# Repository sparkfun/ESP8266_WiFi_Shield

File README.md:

SparkFun ESP8266 WiFi Shield
========================================

[*SparkFun ESP8266 WiFi Shield (WRL-13287)*](https://www.sparkfun.com/products/13287)

The [SparkFun ESP8266 WiFi Shield](https://www.sparkfun.com/products/13287) is essentially an Arduino shield for the ESP8266 WiFi SoC. The ESP8266 ships with a slightly customized version of the Espressif AT command set.

The ESP8266 is controlled by serial AT commands. The shield is equipped with a switch to swap between a software serial port or hardware serial port interface.

Repository Contents
-------------------

* **/Firmware** - Firmware flashed on the ESP8266 WiFi Shield (requires ESP8266 SDK 1.2.0)
* **/Hardware** - Eagle design files (.brd, .sch)
* **/Production** - Production panel files (.brd)

Documentation
--------------
* **[Hookup Guide](https://learn.sparkfun.com/tutorials/esp8266-wifi-shield-hookup-guide)** - Exhaustive hookup guide for the ESP8266 WiFi Shield.

Product Versions
----------------
* [DEV-13287](https://www.sparkfun.com/products/13287)- V1.0 release of the WiFi Shield.

License Information
-------------------
This product is _**open source**_! 

The **hardware** is released under [Creative Commons ShareAlike 4.0 International](https://creativecommons.org/licenses/by-sa/4.0/).

The **code** is beerware; if you see me (or any other SparkFun employee) at the local, and you've found our code helpful, please buy us a round!

Please use, reuse, and modify these files as you see fit. Please maintain attribution to SparkFun Electronics and release anyWiFi Shield derivative under the same license.

Distributed as-is; no warranty is given.

- Your friends at SparkFun.

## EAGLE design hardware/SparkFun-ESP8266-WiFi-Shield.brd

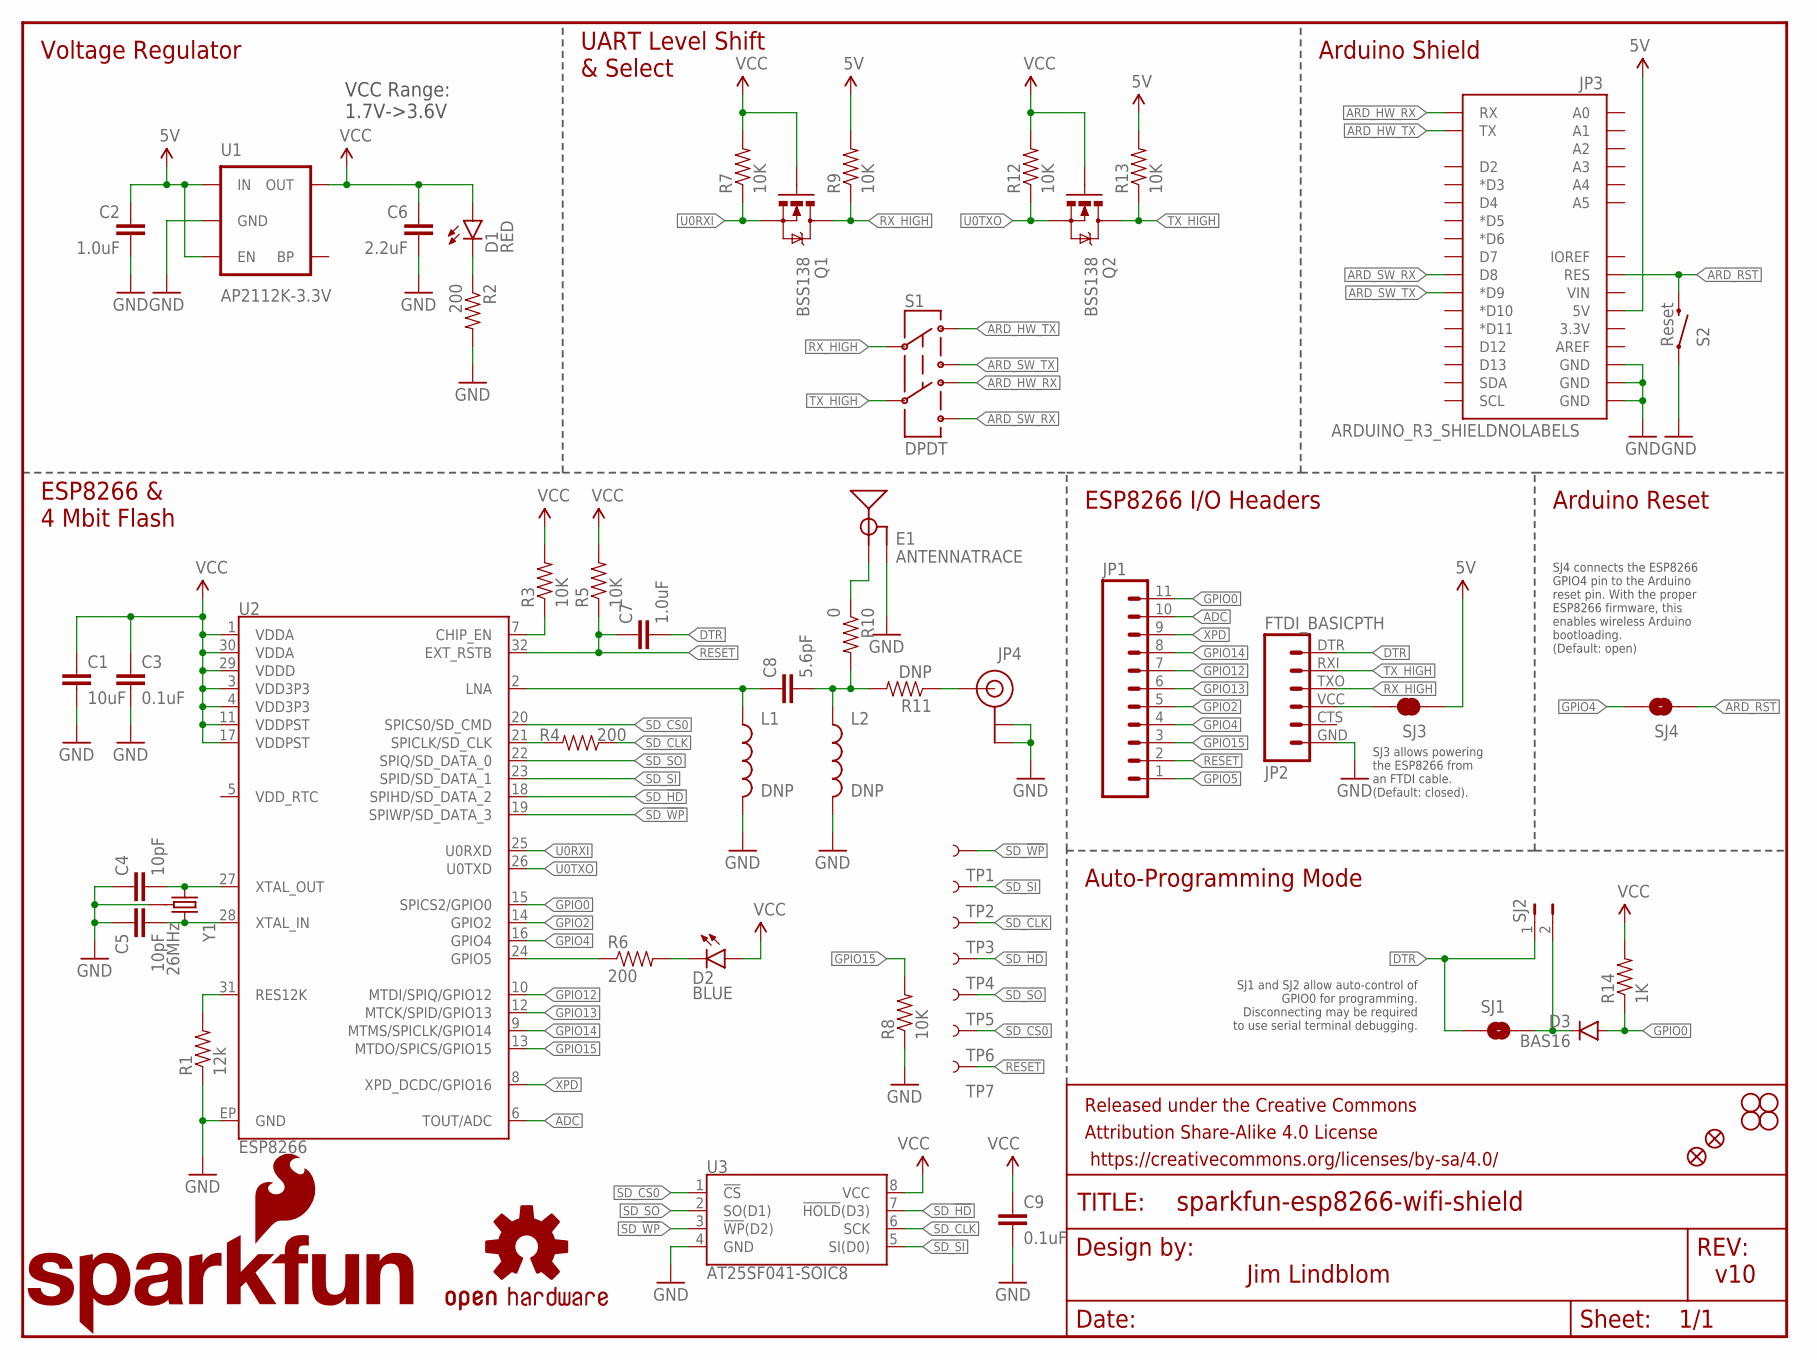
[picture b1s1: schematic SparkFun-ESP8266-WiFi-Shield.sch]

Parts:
C1: 10uF; 0603-CAP
C2: 1.0uF; 0805
C3, C9: 0.1uF; 0603-CAP
C4, C5: 10pF; 0603-CAP
C6: 2.2uF; 0603-CAP
C7: 1.0uF; 0603-CAP
C8: 5.6pF; 0603-CAP
D1: RED; LED-0603
D2: BLUE; LED-0603
D3: BAS16; SOD-323
E1: ANTENNATRACE; TRACE_ANTENNA_2.4GHZ_25.7MM
FID1, FID2: FIDUCIAL1X2; FIDUCIAL-1X2
FRAME1: FRAME-LETTER; CREATIVE_COMMONS
JP1: M11PTH; 1X11
JP2: FTDI_BASICPTH; FTDI_BASIC
JP3: ARDUINO_R3_SHIELDNOLABELS; UNO_R3_SHIELD_NOLABELS
JP4: U.FL
L1, L2: DNP; 0603
LOGO1: SFE_LOGO_NAME_FLAME.2_INCH; SFE_LOGO_NAME_FLAME_.2
LOGO2: OSHW-LOGOM; OSHW-LOGO-M
Q1, Q2: BSS138; SOT23-3
R1: 12k; 0603-RES
R2, R4, R6: 200; 0603-RES
R3, R5, R7, R8, R9, R12, R13: 10K; 0603-RES
R10: 0; 0603
R11: DNP; 0603-RES
R14: 1K; 0603-RES
S1: DPDT; AYZ0202
S2: Reset; TACTILE-SWITCH-SMD
SJ1: JUMPER-PAD-2-NO; PAD-JUMPER-2-NO_NO_SILK
SJ2: JUMPER-PTH-2-NO; PTH-JUMPER-2-NO_NO_SILK
SJ3: JUMPER-PAD-2-NC_BY_TRACE; PAD-JUMPER-2-NC_BY_TRACE_YES_SILK
SJ4: JUMPER-PAD-2-NOYES_SILK; PAD-JUMPER-2-NO_YES_SILK
STANDOFF1, STANDOFF2, STANDOFF3, STANDOFF4: STAND-OFF
TP1, TP2, TP3, TP4, TP5, TP6, TP7: TEST-POINT3X5; PAD.03X.05
U1: AP2112K-3.3V; SOT23-5
U2: ESP8266; QFN32
U3: AT25SF041-SOIC8; SO08
Y1: 26MHz; CRYSTAL-SMD-3.2X2.5

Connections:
5V: C2.1, JP3.5V, R9.2, R13.2, SJ3.1, U1.1 (IN), U1.3 (EN)
ADC: JP1.10, U2.6 (TOUT/ADC)
ANT: JP4.P$3 (SIGNAL), R11.1
ARD_HW_RX: JP3.RX, S1.4
ARD_HW_TX: JP3.TX, S1.1
ARD_RST: JP3.RES, S2.3 (2), SJ4.1
ARD_SW_RX: JP3.D8, S1.6
ARD_SW_TX: JP3.D9 (*D9), S1.3
CHIP_EN: R3.1, U2.7 (CHIP_EN)
DTR: C7.2, JP2.DTR (1), SJ1.1, SJ2.1
GND: C1.2, C2.2, C3.2, C4.1, C5.1, C6.2, C9.2, E1.GND, E1.GND2 (GND), JP2.GND (6), JP3.GND@0 (GND), JP3.GND@1 (GND), JP3.GND@2 (GND), JP4.P$1 (GND), JP4.P$2 (GND), L1.2, L2.2, R1.1, R2.2, R8.1, S2.1, U1.2 (GND), U2.EP (GND), U3.4 (GND), Y1.2 (GND), Y1.4 (GND)
GPIO0: D3.A, JP1.11, R14.1, U2.15 (SPICS2/GPIO0)
GPIO2: JP1.5, U2.14 (GPIO2)
GPIO4: JP1.4, SJ4.2, U2.16 (GPIO4)
GPIO5: JP1.1, R6.1, U2.24 (GPIO5)
GPIO12: JP1.7, U2.10 (MTDI/SPIQ/GPIO12)
GPIO13: JP1.6, U2.12 (MTCK/SPID/GPIO13)
GPIO14: JP1.8, U2.9 (MTMS/SPICLK/GPIO14)
GPIO15: JP1.3, R8.2, U2.13 (MTDO/SPICS/GPIO15)
LNA: C8.1, L1.1, U2.2 (LNA)
unnamed: R1.2, U2.31 (RES12K)
unnamed: C5.2, U2.28 (XTAL_IN), Y1.3 (2)
unnamed: C4.2, U2.27 (XTAL_OUT), Y1.1
unnamed: D1.C, R2.1
unnamed: C8.2, L2.1, R10.2, R11.2
unnamed: R4.2, U2.21 (SPICLK/SD_CLK)
unnamed: JP2.VCC (4), SJ3.2
unnamed: D2.C, R6.2
RESET: C7.1, JP1.2, R5.1, TP7.P$1, U2.32 (EXT_RSTB)
RX_HIGH: JP2.TXO (3), Q1.3 (D), R9.1, S1.2
SD_!HD!: TP4.P$1, U2.18 (SPIHD/SD_DATA_2), U3.7 (!HOLD!(D3))
SD_!WP!: TP1.P$1, U2.19 (SPIWP/SD_DATA_3), U3.3 (!WP!(D2))
SD_CLK: R4.1, TP3.P$1, U3.6 (SCK)
SD_CS0: TP6.P$1, U2.20 (SPICS0/SD_CMD), U3.1 (!CS!)
SD_SI: TP2.P$1, U2.23 (SPID/SD_DATA_1), U3.5 (SI(D0))
SD_SO: TP5.P$1, U2.22 (SPIQ/SD_DATA_0), U3.2 (SO(D1))
SJ2: D3.C, SJ1.2, SJ2.2
TRACE_ANT: E1.ANT (SIGNAL), R10.1
TX_HIGH: JP2.RXI (2), Q2.3 (D), R13.1, S1.5
U0RXI: Q1.2 (S), R7.1, U2.25 (U0RXD)
U0TXO: Q2.2 (S), R12.1, U2.26 (U0TXD)
VCC: C1.1, C3.1, C6.1, C9.1, D1.A, D2.A, Q1.1 (G), Q2.1 (G), R3.2, R5.2, R7.2, R12.2, R14.2, U1.5 (OUT), U2.1 (VDDA), U2.3 (VDD3P3), U2.4 (VDD3P3), U2.11 (VDDPST), U2.17 (VDDPST), U2.29 (VDDD), U2.30 (VDDA), U3.8 (VCC)
XPD: JP1.9, U2.8 (XPD_DCDC/GPIO16)

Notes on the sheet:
VCC Range: 1.7V->3.6V
SJ1 and SJ2 allow auto-control of GPIO0 for programming. Disconnecting may be required to use serial terminal debugging.
Auto-Programming Mode
ESP8266 I/O Headers
Arduino Shield
UART Level Shift & Select
Voltage Regulator
ESP8266 & 4 Mbit Flash
v10
Jim Lindblom
Arduino Reset
SJ4 connects the ESP8266 GPIO4 pin to the Arduino reset pin. With the proper ESP8266 firmware, this enables wireless Arduino bootloading. (Default: open)
SJ3 allows powering the ESP8266 from an FTDI cable. (Default: closed).

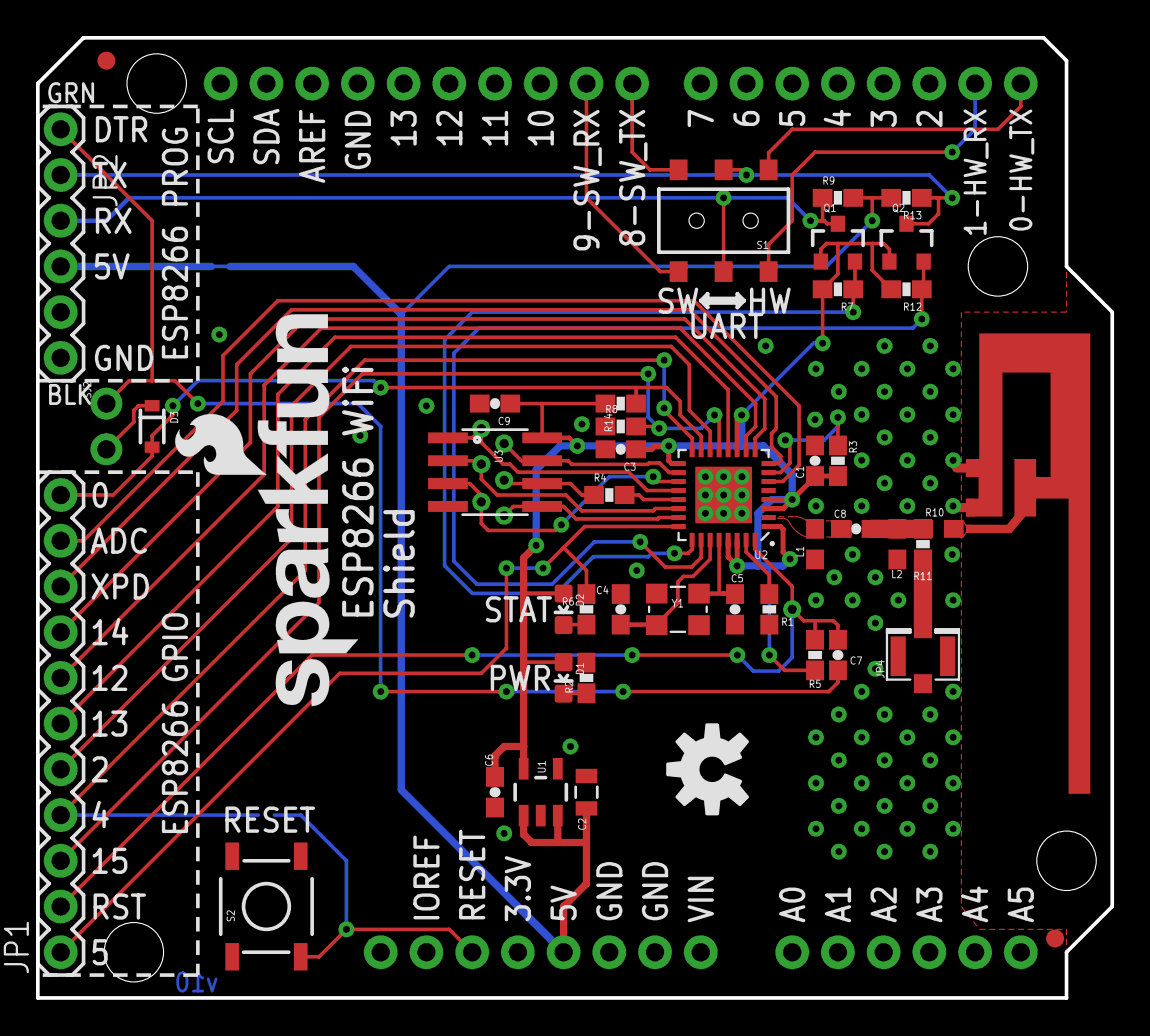
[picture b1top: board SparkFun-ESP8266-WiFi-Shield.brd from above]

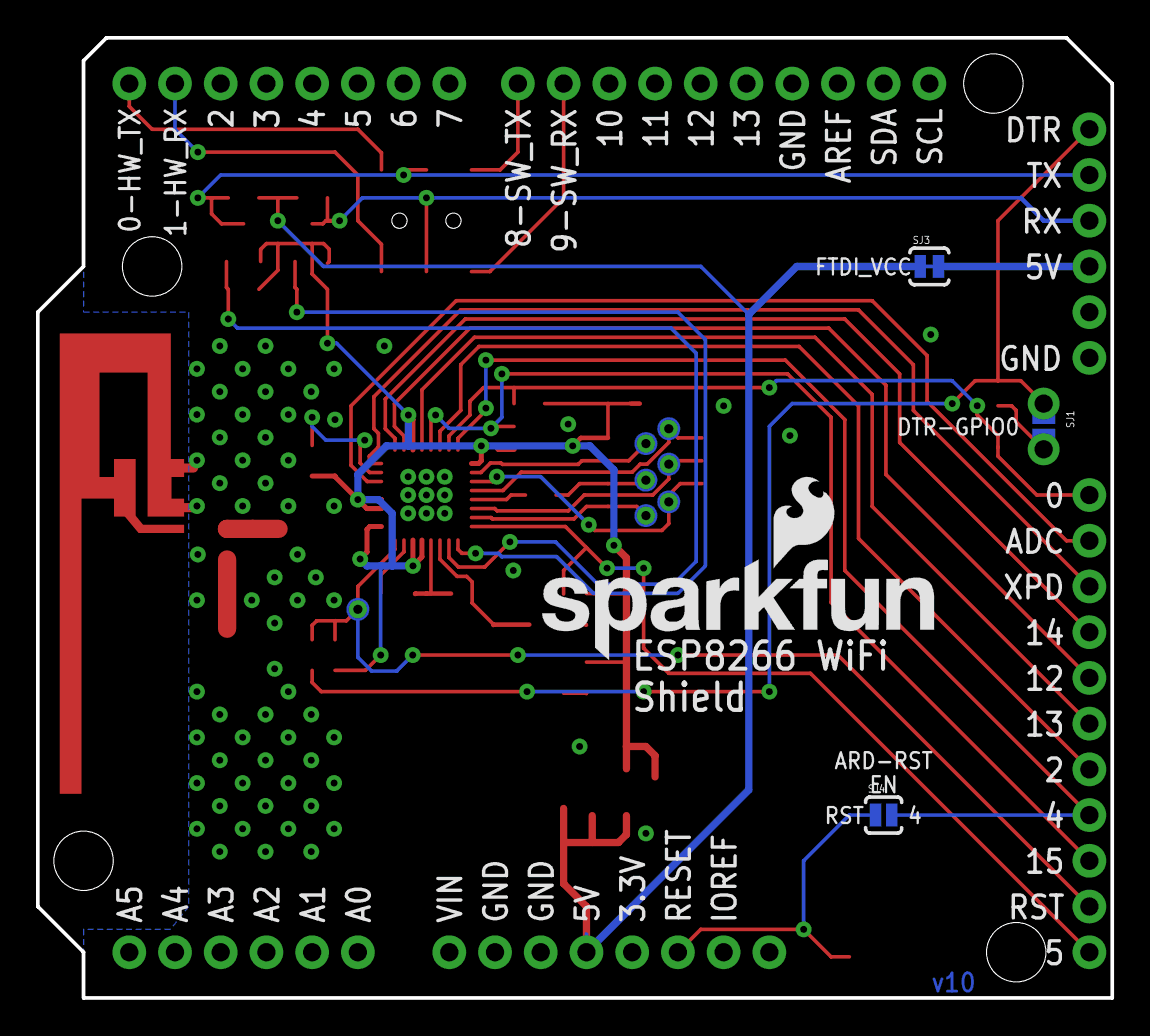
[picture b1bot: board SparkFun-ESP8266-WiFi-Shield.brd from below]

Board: 2 copper layers, 59.7 x 53.3 mm, 62 parts (11 on the bottom side), 43 nets.

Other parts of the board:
LOGO3: SFE_LOGO_NAME_FLAME.2_INCH; SFE_LOGO_NAME_FLAME_.2

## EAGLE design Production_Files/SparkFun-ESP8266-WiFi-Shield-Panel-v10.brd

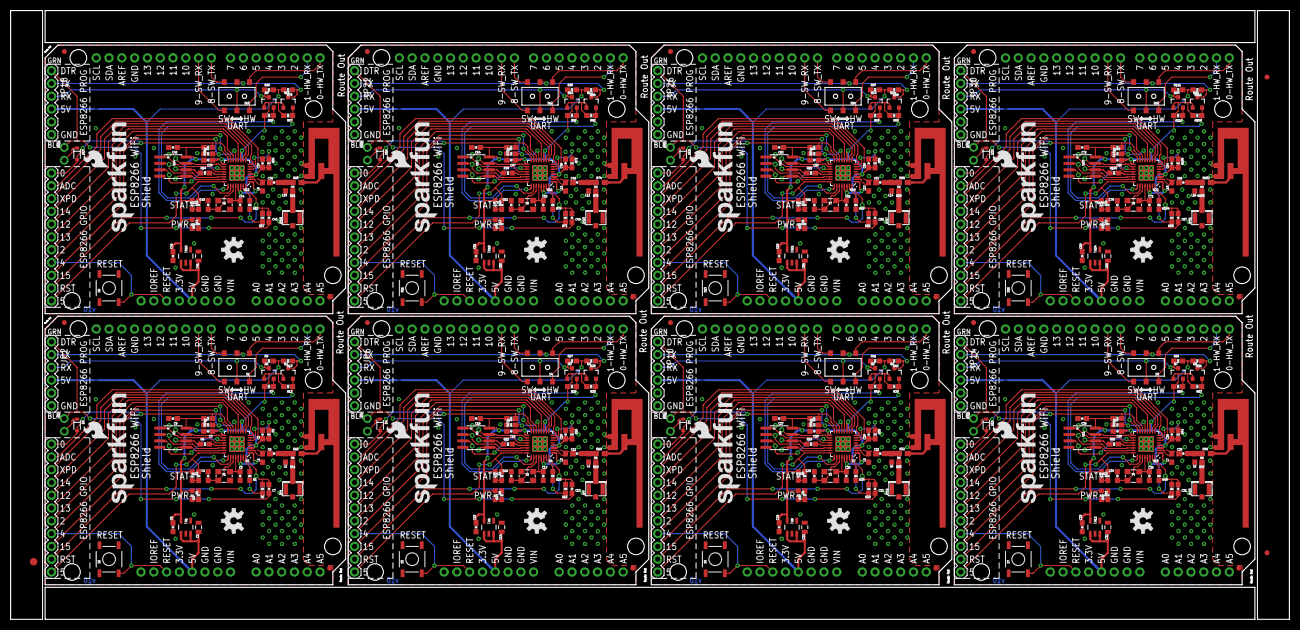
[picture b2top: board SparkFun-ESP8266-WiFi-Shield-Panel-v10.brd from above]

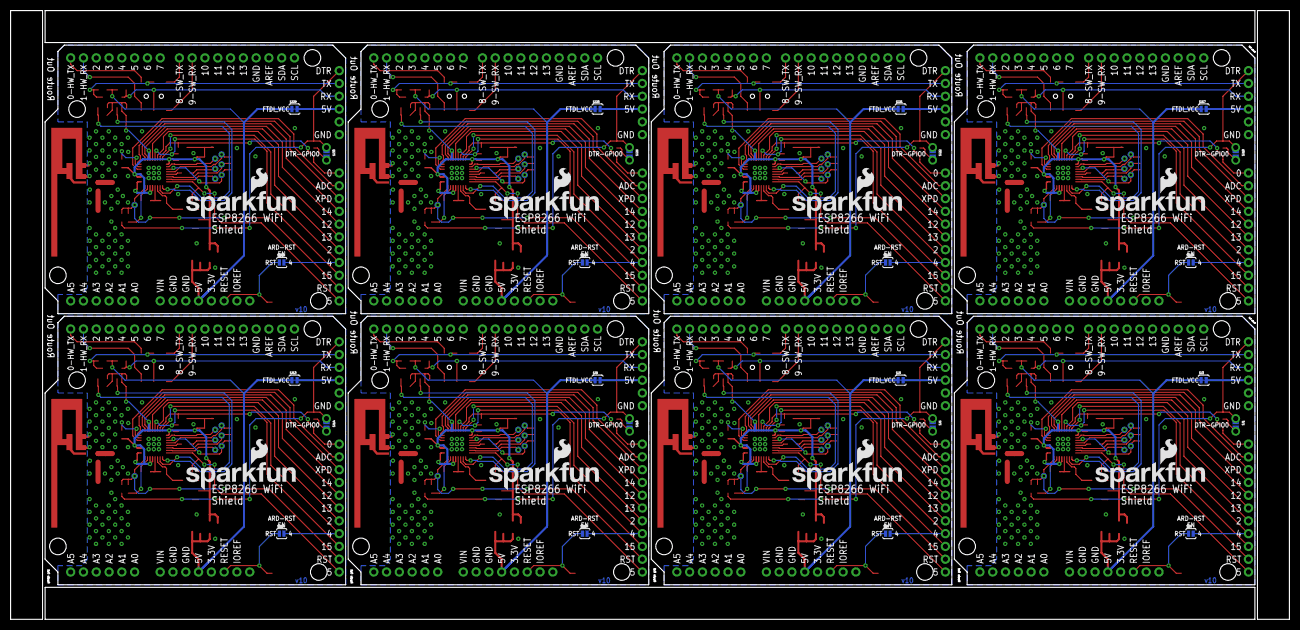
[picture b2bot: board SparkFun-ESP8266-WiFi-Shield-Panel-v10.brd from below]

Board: 2 copper layers, 254.0 x 120.9 mm, 491 parts (88 on the bottom side), 344 nets.

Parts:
C1, C10, C19, C28, C37, C46, C55, C64: 10uF; 0603-CAP
C2, C14, C23, C32, C41, C50, C59, C68: 1.0uF; 0805
C3, C9, C11, C18, C20, C27, C29, C36, C38, C45, C47, C54, C56, C63, C65, C72: 0.1uF; 0603-CAP
C4, C5, C16, C17, C25, C26, C34, C35, C43, C44, C52, C53, C61, C62, C70, C71: 10pF; 0603-CAP
C6, C15, C24, C33, C42, C51, C60, C69: 2.2uF; 0603-CAP
C7, C13, C22, C31, C40, C49, C58, C67: 1.0uF; 0603-CAP
C8, C12, C21, C30, C39, C48, C57, C66: 5.6pF; 0603-CAP
D1, D5, D8, D11, D14, D17, D20, D23: RED; LED-0603
D2, D6, D9, D12, D15, D18, D21, D24: BLUE; LED-0603
D3, D4, D7, D10, D13, D16, D19, D22: BAS16; SOD-323
E1, E2, E3, E4, E5, E6, E7, E8: ANTENNATRACE; TRACE_ANTENNA_2.4GHZ_25.7MM
E$1: FIDUCIAL-1.5X3
E$4, E$5: FIDUCIAL-1X2
FID1, FID2, FID3, FID4, FID5, FID6, FID7, FID8, FID9, FID10, FID11, FID12, FID13, FID14, FID15, FID16: FIDUCIAL1X2; FIDUCIAL-1X2
JP1, JP8, JP12, JP16, JP20, JP24, JP28, JP32: 1X11
JP2, JP6, JP10, JP14, JP18, JP22, JP26, JP30: FTDI_BASICPTH; FTDI_BASIC
JP3, JP5, JP9, JP13, JP17, JP21, JP25, JP29: ARDUINO_R3_SHIELDNOLABELS; UNO_R3_SHIELD_NOLABELS
JP4, JP7, JP11, JP15, JP19, JP23, JP27, JP31: U.FL
L1, L2, L3, L4, L5, L6, L7, L8, L9, L10, L11, L12, L13, L14, L15, L16: DNP; 0603
LOGO1, LOGO3, LOGO5, LOGO6, LOGO8, LOGO9, LOGO11, LOGO12, LOGO14, LOGO15, LOGO17, LOGO18, LOGO20, LOGO21, LOGO23, LOGO24: SFE_LOGO_NAME_FLAME.2_INCH; SFE_LOGO_NAME_FLAME_.2
LOGO2, LOGO4, LOGO7, LOGO10, LOGO13, LOGO16, LOGO19, LOGO22: OSHW-LOGOM; OSHW-LOGO-M
Q1, Q2, Q3, Q4, Q5, Q6, Q7, Q8, Q9, Q10, Q11, Q12, Q13, Q14, Q15, Q16: BSS138; SOT23-3
R1, R20, R34, R48, R62, R76, R90, R104: 12k; 0603-RES
R2, R4, R6, R21, R22, R23, R35, R36, R37, R49, R50, R51, R63, R64, R65, R77, R78, R79, R91, R92, R93, R105, R106, R107: 200; 0603-RES
R3, R5, R7, R8, R9, R12, R13, R15, R16, R24, R25, R26, R27, R28, R29, R30, R38, R39, R40, R41, R42, R43, R44, R52, R53, R54, R55, R56, R57, R58, R66, R67, R68, R69, R70, R71, R72, R80, R81, R82, R83, R84, R85, R86, R94, R95, R96, R97, R98, R99, R100, R108, R109, R110, R111, R112: 10K; 0603-RES
R10, R18, R32, R46, R60, R74, R88, R102: 0; 0603
R11, R19, R33, R47, R61, R75, R89, R103: DNP; 0603-RES
R14, R17, R31, R45, R59, R73, R87, R101: 1K; 0603-RES
S1, S4, S6, S8, S10, S12, S14, S16: DPDT; AYZ0202
S2, S3, S5, S7, S9, S11, S13, S15: Reset; TACTILE-SWITCH-SMD
SJ1, SJ6, SJ10, SJ14, SJ18, SJ22, SJ26, SJ30: PAD-JUMPER-2-NO_NO_SILK
SJ2, SJ7, SJ11, SJ15, SJ19, SJ23, SJ27, SJ31: PTH-JUMPER-2-NO_NO_SILK
SJ3, SJ5, SJ9, SJ13, SJ17, SJ21, SJ25, SJ29: PAD-JUMPER-2-NC_BY_TRACE_YES_SILK
SJ4, SJ8, SJ12, SJ16, SJ20, SJ24, SJ28, SJ32: PAD-JUMPER-2-NO_YES_SILK
STANDOFF1, STANDOFF2, STANDOFF3, STANDOFF4, STANDOFF5, STANDOFF6, STANDOFF7, STANDOFF8, STANDOFF9, STANDOFF10, STANDOFF11, STANDOFF12, STANDOFF13, STANDOFF14, STANDOFF15, STANDOFF16, STANDOFF17, STANDOFF18, STANDOFF19, STANDOFF20, STANDOFF21, STANDOFF22, STANDOFF23, STANDOFF24, STANDOFF25, STANDOFF26, STANDOFF27, STANDOFF28, STANDOFF29, STANDOFF30, STANDOFF31, STANDOFF32: STAND-OFF
TP1, TP2, TP3, TP4, TP5, TP6, TP7, TP8, TP9, TP10, TP11, TP12, TP13, TP14, TP15, TP16, TP17, TP18, TP19, TP20, TP21, TP22, TP23, TP24, TP25, TP26, TP27, TP28, TP29, TP30, TP31, TP32, TP33, TP34, TP35, TP36, TP37, TP38, TP39, TP40, TP41, TP42, TP43, TP44, TP45, TP46, TP47, TP48, TP49, TP50, TP51, TP52, TP53, TP54, TP55, TP56: PAD.03X.05
U1, U6, U9, U12, U15, U18, U21, U24: AP2112K-3.3V; SOT23-5
U2, U4, U7, U10, U13, U16, U19, U22: ESP8266; QFN32
U3, U5, U8, U11, U14, U17, U20, U23: AT25SF041-SOIC8; SO08
Y1, Y2, Y3, Y4, Y5, Y6, Y7, Y8: 26MHz; CRYSTAL-SMD-3.2X2.5

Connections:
5V: C2.1, JP3.5V, R9.2, R13.2, SJ3.1, U1.1, U1.3
5V1: C14.1, JP5.5V, R27.2, R28.2, SJ5.1, U6.1, U6.3
5V2: C23.1, JP9.5V, R41.2, R42.2, SJ9.1, U9.1, U9.3
5V3: C32.1, JP13.5V, R55.2, R56.2, SJ13.1, U12.1, U12.3
5V4: C41.1, JP17.5V, R69.2, R70.2, SJ17.1, U15.1, U15.3
5V5: C50.1, JP21.5V, R83.2, R84.2, SJ21.1, U18.1, U18.3
5V6: C59.1, JP25.5V, R97.2, R98.2, SJ25.1, U21.1, U21.3
5V7: C68.1, JP29.5V, R111.2, R112.2, SJ29.1, U24.1, U24.3
ADC: JP1.10, U2.6
ADC1: JP8.10, U4.6
ADC2: JP12.10, U7.6
ADC3: JP16.10, U10.6
ADC4: JP20.10, U13.6
ADC5: JP24.10, U16.6
ADC6: JP28.10, U19.6
ADC7: JP32.10, U22.6
ANT: JP4.P$3, R11.1
ANT1: JP7.P$3, R19.1
ANT2: JP11.P$3, R33.1
ANT3: JP15.P$3, R47.1
ANT4: JP19.P$3, R61.1
ANT5: JP23.P$3, R75.1
ANT6: JP27.P$3, R89.1
ANT7: JP31.P$3, R103.1
ARD_HW_RX: JP3.RX, S1.4
ARD_HW_RX1: JP5.RX, S4.4
ARD_HW_RX2: JP9.RX, S6.4
ARD_HW_RX3: JP13.RX, S8.4
ARD_HW_RX4: JP17.RX, S10.4
ARD_HW_RX5: JP21.RX, S12.4
ARD_HW_RX6: JP25.RX, S14.4
ARD_HW_RX7: JP29.RX, S16.4
ARD_HW_TX: JP3.TX, S1.1
ARD_HW_TX1: JP5.TX, S4.1
ARD_HW_TX2: JP9.TX, S6.1
ARD_HW_TX3: JP13.TX, S8.1
ARD_HW_TX4: JP17.TX, S10.1
ARD_HW_TX5: JP21.TX, S12.1
ARD_HW_TX6: JP25.TX, S14.1
ARD_HW_TX7: JP29.TX, S16.1
ARD_RST: JP3.RES, S2.3, SJ4.1
ARD_RST1: JP5.RES, S3.3, SJ8.1
ARD_RST2: JP9.RES, S5.3, SJ12.1
ARD_RST3: JP13.RES, S7.3, SJ16.1
ARD_RST4: JP17.RES, S9.3, SJ20.1
ARD_RST5: JP21.RES, S11.3, SJ24.1
ARD_RST6: JP25.RES, S13.3, SJ28.1
ARD_RST7: JP29.RES, S15.3, SJ32.1
ARD_SW_RX: JP3.D8, S1.6
ARD_SW_RX1: JP5.D8, S4.6
ARD_SW_RX2: JP9.D8, S6.6
ARD_SW_RX3: JP13.D8, S8.6
ARD_SW_RX4: JP17.D8, S10.6
ARD_SW_RX5: JP21.D8, S12.6
ARD_SW_RX6: JP25.D8, S14.6
ARD_SW_RX7: JP29.D8, S16.6
ARD_SW_TX: JP3.D9, S1.3
ARD_SW_TX1: JP5.D9, S4.3
ARD_SW_TX2: JP9.D9, S6.3
ARD_SW_TX3: JP13.D9, S8.3
ARD_SW_TX4: JP17.D9, S10.3
ARD_SW_TX5: JP21.D9, S12.3
ARD_SW_TX6: JP25.D9, S14.3
ARD_SW_TX7: JP29.D9, S16.3
CHIP_EN: R3.1, U2.7
CHIP_EN1: R16.1, U4.7
CHIP_EN2: R30.1, U7.7
CHIP_EN3: R44.1, U10.7
CHIP_EN4: R58.1, U13.7
CHIP_EN5: R72.1, U16.7
CHIP_EN6: R86.1, U19.7
CHIP_EN7: R100.1, U22.7
DTR: C7.2, JP2.DTR, SJ1.1, SJ2.1
DTR1: C13.2, JP6.DTR, SJ6.1, SJ7.1
DTR2: C22.2, JP10.DTR, SJ10.1, SJ11.1
DTR3: C31.2, JP14.DTR, SJ14.1, SJ15.1
DTR4: C40.2, JP18.DTR, SJ18.1, SJ19.1
DTR5: C49.2, JP22.DTR, SJ22.1, SJ23.1
DTR6: C58.2, JP26.DTR, SJ26.1, SJ27.1
DTR7: C67.2, JP30.DTR, SJ30.1, SJ31.1
GND: C1.2, C2.2, C3.2, C4.1, C5.1, C6.2, C9.2, E1.GND, E1.GND2, JP2.GND, JP3.GND@0, JP3.GND@1, JP3.GND@2, JP4.P$1, JP4.P$2, L1.2, L2.2, R1.1, R2.2, R8.1, S2.1, U1.2, U2.EP, U3.4, Y1.2, Y1.4
GND1: C10.2, C11.2, C14.2, C15.2, C16.1, C17.1, C18.2, E2.GND, E2.GND2, JP5.GND@0, JP5.GND@1, JP5.GND@2, JP6.GND, JP7.P$1, JP7.P$2, L3.2, L4.2, R20.1, R23.2, R24.1, S3.1, U4.EP, U5.4, U6.2, Y2.2, Y2.4
GND2: C19.2, C20.2, C23.2, C24.2, C25.1, C26.1, C27.2, E3.GND, E3.GND2, JP9.GND@0, JP9.GND@1, JP9.GND@2, JP10.GND, JP11.P$1, JP11.P$2, L5.2, L6.2, R34.1, R37.2, R38.1, S5.1, U7.EP, U8.4, U9.2, Y3.2, Y3.4
GND3: C28.2, C29.2, C32.2, C33.2, C34.1, C35.1, C36.2, E4.GND, E4.GND2, JP13.GND@0, JP13.GND@1, JP13.GND@2, JP14.GND, JP15.P$1, JP15.P$2, L7.2, L8.2, R48.1, R51.2, R52.1, S7.1, U10.EP, U11.4, U12.2, Y4.2, Y4.4
GND4: C37.2, C38.2, C41.2, C42.2, C43.1, C44.1, C45.2, E5.GND, E5.GND2, JP17.GND@0, JP17.GND@1, JP17.GND@2, JP18.GND, JP19.P$1, JP19.P$2, L9.2, L10.2, R62.1, R65.2, R66.1, S9.1, U13.EP, U14.4, U15.2, Y5.2, Y5.4
GND5: C46.2, C47.2, C50.2, C51.2, C52.1, C53.1, C54.2, E6.GND, E6.GND2, JP21.GND@0, JP21.GND@1, JP21.GND@2, JP22.GND, JP23.P$1, JP23.P$2, L11.2, L12.2, R76.1, R79.2, R80.1, S11.1, U16.EP, U17.4, U18.2, Y6.2, Y6.4
GND6: C55.2, C56.2, C59.2, C60.2, C61.1, C62.1, C63.2, E7.GND, E7.GND2, JP25.GND@0, JP25.GND@1, JP25.GND@2, JP26.GND, JP27.P$1, JP27.P$2, L13.2, L14.2, R90.1, R93.2, R94.1, S13.1, U19.EP, U20.4, U21.2, Y7.2, Y7.4
GND7: C64.2, C65.2, C68.2, C69.2, C70.1, C71.1, C72.2, E8.GND, E8.GND2, JP29.GND@0, JP29.GND@1, JP29.GND@2, JP30.GND, JP31.P$1, JP31.P$2, L15.2, L16.2, R104.1, R107.2, R108.1, S15.1, U22.EP, U23.4, U24.2, Y8.2, Y8.4
GPIO0: D3.A, JP1.11, R14.1, U2.15
GPIO1: JP8.8, U4.9
GPIO2: JP1.5, U2.14
GPIO3: D4.A, JP8.11, R17.1, U4.15
GPIO4: JP1.4, SJ4.2, U2.16
GPIO5: JP1.1, R6.1, U2.24
GPIO6: JP8.1, R21.1, U4.24
GPIO7: JP8.4, SJ8.2, U4.16
GPIO8: JP8.3, R24.2, U4.13
GPIO9: JP8.6, U4.12
GPIO10: JP8.7, U4.10
GPIO11: JP8.5, U4.14
GPIO12: JP1.7, U2.10
GPIO13: JP1.6, U2.12
GPIO14: JP1.8, U2.9
GPIO15: JP1.3, R8.2, U2.13
GPIO16: JP12.8, U7.9
GPIO17: D7.A, JP12.11, R31.1, U7.15
GPIO18: JP12.1, R35.1, U7.24
GPIO19: JP12.4, SJ12.2, U7.16
GPIO20: JP12.3, R38.2, U7.13
GPIO21: JP12.6, U7.12
GPIO22: JP12.7, U7.10
GPIO23: JP12.5, U7.14
GPIO24: JP16.8, U10.9
GPIO25: D10.A, JP16.11, R45.1, U10.15
GPIO26: JP16.1, R49.1, U10.24
GPIO27: JP16.4, SJ16.2, U10.16
GPIO28: JP16.3, R52.2, U10.13
GPIO29: JP16.6, U10.12
GPIO30: JP16.7, U10.10
GPIO31: JP16.5, U10.14
GPIO32: JP20.8, U13.9
GPIO33: D13.A, JP20.11, R59.1, U13.15
GPIO34: JP20.1, R63.1, U13.24
GPIO35: JP20.4, SJ20.2, U13.16
GPIO36: JP20.3, R66.2, U13.13
GPIO37: JP20.6, U13.12
GPIO38: JP20.7, U13.10
GPIO39: JP20.5, U13.14
GPIO40: JP24.8, U16.9
GPIO41: D16.A, JP24.11, R73.1, U16.15
GPIO42: JP24.1, R77.1, U16.24
GPIO43: JP24.4, SJ24.2, U16.16
GPIO44: JP24.3, R80.2, U16.13
GPIO45: JP24.6, U16.12
GPIO46: JP24.7, U16.10
GPIO47: JP24.5, U16.14
GPIO48: JP28.8, U19.9
GPIO49: D19.A, JP28.11, R87.1, U19.15
GPIO50: JP28.1, R91.1, U19.24
GPIO51: JP28.4, SJ28.2, U19.16
GPIO52: JP28.3, R94.2, U19.13
GPIO53: JP28.6, U19.12
GPIO54: JP28.7, U19.10
GPIO55: JP28.5, U19.14
GPIO56: JP32.8, U22.9
GPIO57: D22.A, JP32.11, R101.1, U22.15
GPIO58: JP32.1, R105.1, U22.24
GPIO59: JP32.4, SJ32.2, U22.16
GPIO60: JP32.3, R108.2, U22.13
GPIO61: JP32.6, U22.12
GPIO62: JP32.7, U22.10
GPIO63: JP32.5, U22.14
LNA: C8.1, L1.1, U2.2
LNA1: C12.1, L3.1, U4.2
LNA2: C21.1, L5.1, U7.2
LNA3: C30.1, L7.1, U10.2
LNA4: C39.1, L9.1, U13.2
LNA5: C48.1, L11.1, U16.2
LNA6: C57.1, L13.1, U19.2
LNA7: C66.1, L15.1, U22.2
unnamed: R1.2, U2.31
unnamed: C5.2, U2.28, Y1.3
unnamed: C4.2, U2.27, Y1.1
unnamed: D1.C, R2.1
unnamed: C8.2, L2.1, R10.2, R11.2
unnamed: R4.2, U2.21
unnamed: JP2.VCC, SJ3.2
unnamed: R20.2, U4.31
unnamed: D2.C, R6.2
unnamed: C17.2, U4.28, Y2.3
unnamed: C16.2, U4.27, Y2.1
unnamed: C12.2, L4.1, R18.2, R19.2
unnamed: R22.2, U4.21
unnamed: D5.C, R23.1
unnamed: JP6.VCC, SJ5.2
unnamed: D6.C, R21.2
unnamed: R34.2, U7.31
unnamed: C26.2, U7.28, Y3.3
unnamed: C25.2, U7.27, Y3.1
unnamed: C21.2, L6.1, R32.2, R33.2
unnamed: R36.2, U7.21
unnamed: D8.C, R37.1
unnamed: JP10.VCC, SJ9.2
unnamed: D9.C, R35.2
unnamed: R48.2, U10.31
unnamed: C35.2, U10.28, Y4.3
unnamed: C34.2, U10.27, Y4.1
unnamed: C30.2, L8.1, R46.2, R47.2
unnamed: R50.2, U10.21
unnamed: D11.C, R51.1
unnamed: JP14.VCC, SJ13.2
unnamed: D12.C, R49.2
unnamed: R62.2, U13.31
unnamed: C44.2, U13.28, Y5.3
unnamed: C43.2, U13.27, Y5.1
unnamed: C39.2, L10.1, R60.2, R61.2
unnamed: R64.2, U13.21
unnamed: D14.C, R65.1
unnamed: JP18.VCC, SJ17.2
unnamed: D15.C, R63.2
unnamed: R76.2, U16.31
unnamed: C53.2, U16.28, Y6.3
unnamed: C52.2, U16.27, Y6.1
unnamed: C48.2, L12.1, R74.2, R75.2
unnamed: R78.2, U16.21
unnamed: D17.C, R79.1
unnamed: JP22.VCC, SJ21.2
unnamed: D18.C, R77.2
unnamed: R90.2, U19.31
unnamed: C62.2, U19.28, Y7.3
unnamed: C61.2, U19.27, Y7.1
unnamed: C57.2, L14.1, R88.2, R89.2
unnamed: R92.2, U19.21
unnamed: D20.C, R93.1
unnamed: JP26.VCC, SJ25.2
unnamed: D21.C, R91.2
unnamed: R104.2, U22.31
unnamed: C71.2, U22.28, Y8.3
unnamed: C70.2, U22.27, Y8.1
unnamed: C66.2, L16.1, R102.2, R103.2
unnamed: R106.2, U22.21
unnamed: D23.C, R107.1
unnamed: JP30.VCC, SJ29.2
unnamed: D24.C, R105.2
RESET: C7.1, JP1.2, R5.1, TP7.P$1, U2.32
RESET1: C13.1, JP8.2, R15.1, TP8.P$1, U4.32
RESET2: C22.1, JP12.2, R29.1, TP15.P$1, U7.32
RESET3: C31.1, JP16.2, R43.1, TP22.P$1, U10.32
RESET4: C40.1, JP20.2, R57.1, TP29.P$1, U13.32
RESET5: C49.1, JP24.2, R71.1, TP36.P$1, U16.32
RESET6: C58.1, JP28.2, R85.1, TP43.P$1, U19.32
RESET7: C67.1, JP32.2, R99.1, TP50.P$1, U22.32
RX_HIGH: JP2.TXO, Q1.3, R9.1, S1.2
RX_HIGH1: JP6.TXO, Q3.3, R27.1, S4.2
RX_HIGH2: JP10.TXO, Q5.3, R41.1, S6.2
RX_HIGH3: JP14.TXO, Q7.3, R55.1, S8.2
RX_HIGH4: JP18.TXO, Q9.3, R69.1, S10.2
RX_HIGH5: JP22.TXO, Q11.3, R83.1, S12.2
RX_HIGH6: JP26.TXO, Q13.3, R97.1, S14.2
RX_HIGH7: JP30.TXO, Q15.3, R111.1, S16.2
SD_!HD!: TP4.P$1, U2.18, U3.7
SD_!HD!1: TP14.P$1, U4.18, U5.7
SD_!HD!2: TP21.P$1, U7.18, U8.7
SD_!HD!3: TP28.P$1, U10.18, U11.7
SD_!HD!4: TP35.P$1, U13.18, U14.7
SD_!HD!5: TP42.P$1, U16.18, U17.7
SD_!HD!6: TP49.P$1, U19.18, U20.7
SD_!HD!7: TP56.P$1, U22.18, U23.7
SD_!WP!: TP1.P$1, U2.19, U3.3
SD_!WP!1: TP11.P$1, U4.19, U5.3
SD_!WP!2: TP18.P$1, U7.19, U8.3
SD_!WP!3: TP25.P$1, U10.19, U11.3
SD_!WP!4: TP32.P$1, U13.19, U14.3
SD_!WP!5: TP39.P$1, U16.19, U17.3
SD_!WP!6: TP46.P$1, U19.19, U20.3
SD_!WP!7: TP53.P$1, U22.19, U23.3
SD_CLK: R4.1, TP3.P$1, U3.6
SD_CLK1: R22.1, TP13.P$1, U5.6
SD_CLK2: R36.1, TP20.P$1, U8.6
SD_CLK3: R50.1, TP27.P$1, U11.6
SD_CLK4: R64.1, TP34.P$1, U14.6
SD_CLK5: R78.1, TP41.P$1, U17.6
SD_CLK6: R92.1, TP48.P$1, U20.6
SD_CLK7: R106.1, TP55.P$1, U23.6
SD_CS0: TP6.P$1, U2.20, U3.1
SD_CS1: TP9.P$1, U4.20, U5.1
SD_CS2: TP16.P$1, U7.20, U8.1
SD_CS3: TP23.P$1, U10.20, U11.1
SD_CS4: TP30.P$1, U13.20, U14.1
SD_CS5: TP37.P$1, U16.20, U17.1
SD_CS6: TP44.P$1, U19.20, U20.1
SD_CS7: TP51.P$1, U22.20, U23.1
SD_SI: TP2.P$1, U2.23, U3.5
SD_SI1: TP12.P$1, U4.23, U5.5
SD_SI2: TP19.P$1, U7.23, U8.5
SD_SI3: TP26.P$1, U10.23, U11.5
SD_SI4: TP33.P$1, U13.23, U14.5
SD_SI5: TP40.P$1, U16.23, U17.5
SD_SI6: TP47.P$1, U19.23, U20.5
SD_SI7: TP54.P$1, U22.23, U23.5
SD_SO: TP5.P$1, U2.22, U3.2
SD_SO1: TP10.P$1, U4.22, U5.2
SD_SO2: TP17.P$1, U7.22, U8.2
SD_SO3: TP24.P$1, U10.22, U11.2
SD_SO4: TP31.P$1, U13.22, U14.2
SD_SO5: TP38.P$1, U16.22, U17.2
SD_SO6: TP45.P$1, U19.22, U20.2
SD_SO7: TP52.P$1, U22.22, U23.2
SJ1: D4.C, SJ6.2, SJ7.2
SJ2: D3.C, SJ1.2, SJ2.2
SJ3: D7.C, SJ10.2, SJ11.2
SJ4: D10.C, SJ14.2, SJ15.2
SJ5: D13.C, SJ18.2, SJ19.2
SJ6: D16.C, SJ22.2, SJ23.2
SJ7: D19.C, SJ26.2, SJ27.2
SJ8: D22.C, SJ30.2, SJ31.2
TRACE_ANT: E1.ANT, R10.1
TRACE_ANT1: E2.ANT, R18.1
TRACE_ANT2: E3.ANT, R32.1
TRACE_ANT3: E4.ANT, R46.1
TRACE_ANT4: E5.ANT, R60.1
TRACE_ANT5: E6.ANT, R74.1
TRACE_ANT6: E7.ANT, R88.1
TRACE_ANT7: E8.ANT, R102.1
TX_HIGH: JP2.RXI, Q2.3, R13.1, S1.5
TX_HIGH1: JP6.RXI, Q4.3, R28.1, S4.5
TX_HIGH2: JP10.RXI, Q6.3, R42.1, S6.5
TX_HIGH3: JP14.RXI, Q8.3, R56.1, S8.5
TX_HIGH4: JP18.RXI, Q10.3, R70.1, S10.5
TX_HIGH5: JP22.RXI, Q12.3, R84.1, S12.5
TX_HIGH6: JP26.RXI, Q14.3, R98.1, S14.5
TX_HIGH7: JP30.RXI, Q16.3, R112.1, S16.5
U0RXI: Q1.2, R7.1, U2.25
U0RXI1: Q3.2, R26.1, U4.25
U0RXI2: Q5.2, R40.1, U7.25
U0RXI3: Q7.2, R54.1, U10.25
U0RXI4: Q9.2, R68.1, U13.25
U0RXI5: Q11.2, R82.1, U16.25
U0RXI6: Q13.2, R96.1, U19.25
U0RXI7: Q15.2, R110.1, U22.25
U0TXO: Q2.2, R12.1, U2.26
U0TXO1: Q4.2, R25.1, U4.26
U0TXO2: Q6.2, R39.1, U7.26
U0TXO3: Q8.2, R53.1, U10.26
U0TXO4: Q10.2, R67.1, U13.26
U0TXO5: Q12.2, R81.1, U16.26
U0TXO6: Q14.2, R95.1, U19.26
U0TXO7: Q16.2, R109.1, U22.26
VCC: C1.1, C3.1, C6.1, C9.1, D1.A, D2.A, Q1.1, Q2.1, R3.2, R5.2, R7.2, R12.2, R14.2, U1.5, U2.1, U2.3, U2.4, U2.11, U2.17, U2.29, U2.30, U3.8
VCC1: C10.1, C11.1, C15.1, C18.1, D5.A, D6.A, Q3.1, Q4.1, R15.2, R16.2, R17.2, R25.2, R26.2, U4.1, U4.3, U4.4, U4.11, U4.17, U4.29, U4.30, U5.8, U6.5
VCC2: C19.1, C20.1, C24.1, C27.1, D8.A, D9.A, Q5.1, Q6.1, R29.2, R30.2, R31.2, R39.2, R40.2, U7.1, U7.3, U7.4, U7.11, U7.17, U7.29, U7.30, U8.8, U9.5
VCC3: C28.1, C29.1, C33.1, C36.1, D11.A, D12.A, Q7.1, Q8.1, R43.2, R44.2, R45.2, R53.2, R54.2, U10.1, U10.3, U10.4, U10.11, U10.17, U10.29, U10.30, U11.8, U12.5
VCC4: C37.1, C38.1, C42.1, C45.1, D14.A, D15.A, Q9.1, Q10.1, R57.2, R58.2, R59.2, R67.2, R68.2, U13.1, U13.3, U13.4, U13.11, U13.17, U13.29, U13.30, U14.8, U15.5
VCC5: C46.1, C47.1, C51.1, C54.1, D17.A, D18.A, Q11.1, Q12.1, R71.2, R72.2, R73.2, R81.2, R82.2, U16.1, U16.3, U16.4, U16.11, U16.17, U16.29, U16.30, U17.8, U18.5
VCC6: C55.1, C56.1, C60.1, C63.1, D20.A, D21.A, Q13.1, Q14.1, R85.2, R86.2, R87.2, R95.2, R96.2, U19.1, U19.3, U19.4, U19.11, U19.17, U19.29, U19.30, U20.8, U21.5
VCC7: C64.1, C65.1, C69.1, C72.1, D23.A, D24.A, Q15.1, Q16.1, R99.2, R100.2, R101.2, R109.2, R110.2, U22.1, U22.3, U22.4, U22.11, U22.17, U22.29, U22.30, U23.8, U24.5
XPD: JP1.9, U2.8
XPD1: JP8.9, U4.8
XPD2: JP12.9, U7.8
XPD3: JP16.9, U10.8
XPD4: JP20.9, U13.8
XPD5: JP24.9, U16.8
XPD6: JP28.9, U19.8
XPD7: JP32.9, U22.8

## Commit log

2015-02-09 Initial commit of hardware.
2015-02-10 Fixing U.FL name and value, minor re-routing.
2015-04-10 Changing STAT LED to active low.
2015-04-10 Connecting GPIO4 to Arduino RST.
    Upping version to v10.
    Should allow for remote bootloading.
    Jumper in-line to disconnect if necessary.
    Defaulting DTR jumpers to open.
2015-04-13 Breaking out ESP8266 reset pin.
    Moved the FTDI header to avoid interfering with screw head.
    Moved position of GPIO5 break out.
    Renamed GPIO16 to XPD.
2015-04-13 Cleaning up schematic.
2015-04-14 Minor mods after running checklist.
2015-04-14 Small re-routes to increase ground plane coverage.
2015-04-21 created panel v10
2015-07-16 Initial commit of firmware.
2015-07-16 Standardizing README.
2015-07-16 Uppercasing 'h' in "Hardware"
2015-07-16 Renaming "Production_Files" folder to "Production"
2015-09-15 Adding binary files flashed in WiFi Shield production.

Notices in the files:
parts and their libraries:
SparkFun-Capacitors: Licensing: Creative Commons ShareAlike 4.0 International - https://creativecommons.org/licenses/by-sa/4.0
SparkFun-Aesthetics: Released under the Creative Commons Attribution Share-Alike 4.0 License
SparkFun-Aesthetics: Released under the Creative Commons
